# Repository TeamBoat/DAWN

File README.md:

# DAWN : De-centralized Atmospheric Weather Network

Contributors: Ken Huang, Christian Molina, Danny Salter

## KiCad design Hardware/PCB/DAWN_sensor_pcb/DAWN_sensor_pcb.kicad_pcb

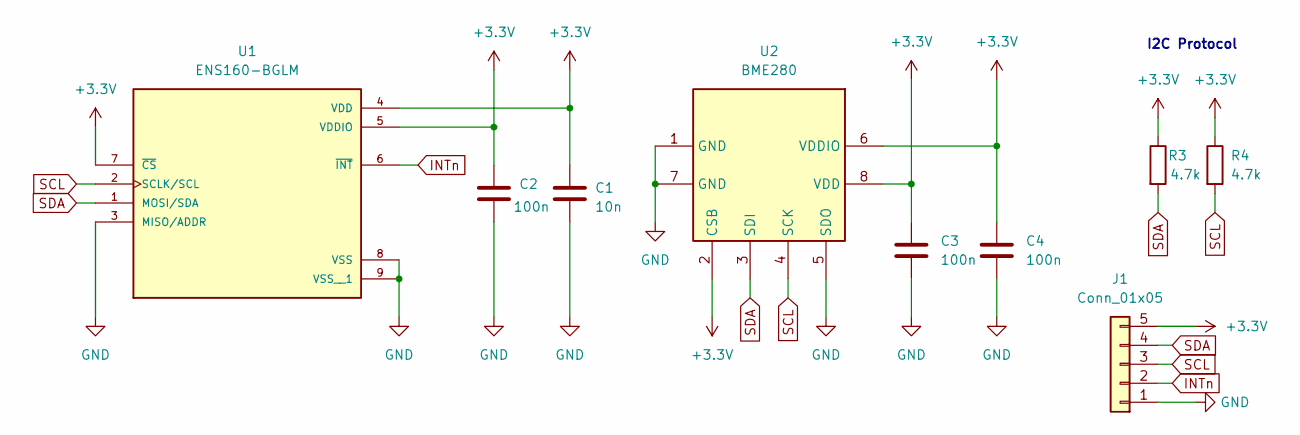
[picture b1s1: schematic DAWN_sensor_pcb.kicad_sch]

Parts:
C1: 10n; C_0805_2012Metric
C2, C3, C4: 100n; C_0805_2012Metric
J1: Conn_01x05; PinHeader_1x05_P2.54mm_Vertical
R3, R4: 4.7k; R_0805_2012Metric
U1: ENS160-BGLM; ENS-160; PARTREV 1.3
U2: BME280; Bosch_LGA-8_2.5x2.5mm_P0.65mm_ClockwisePinNumbering

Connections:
+3.3V: C1.1, C2.1, C3.1, C4.1, J1.5, R3.1, R4.1, U1.4 (VDD), U1.5 (VDDIO), U1.7 (~CS), U2.2 (CSB), U2.6 (VDDIO), U2.8 (VDD)
GND: C1.2, C2.2, C3.2, C4.2, J1.1, U1.3 (MISO/ADDR), U1.8 (VSS), U1.9 (VSS__1), U2.1 (GND), U2.5 (SDO), U2.7 (GND)
INTn: J1.2, U1.6 (~INT)
SCL: J1.3, R4.2, U1.2 (SCLK/SCL), U2.4 (SCK)
SDA: J1.4, R3.2, U1.1 (MOSI/SDA), U2.3 (SDI)

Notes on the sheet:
I2C Protocol

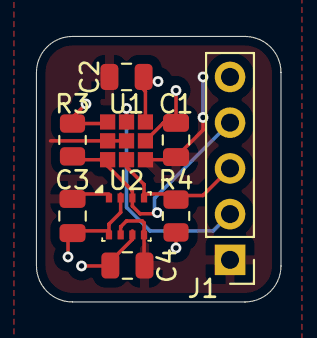
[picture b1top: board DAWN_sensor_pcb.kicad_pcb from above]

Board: 2 copper layers, 13.6 x 14.8 mm, 9 parts (0 on the bottom side), 5 nets.

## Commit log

2024-05-01 Setup
2024-05-03 Export.zip
2024-05-14 Edit Schem
2024-05-31 Push sensor code
2024-06-02 dawn code
2024-06-04 Buzzer Updated
2024-06-04 lora
2024-06-05 DAWN V2
    lora working with ENS160 sensor
2024-06-05 dawnV3
2024-06-06 Lora display
